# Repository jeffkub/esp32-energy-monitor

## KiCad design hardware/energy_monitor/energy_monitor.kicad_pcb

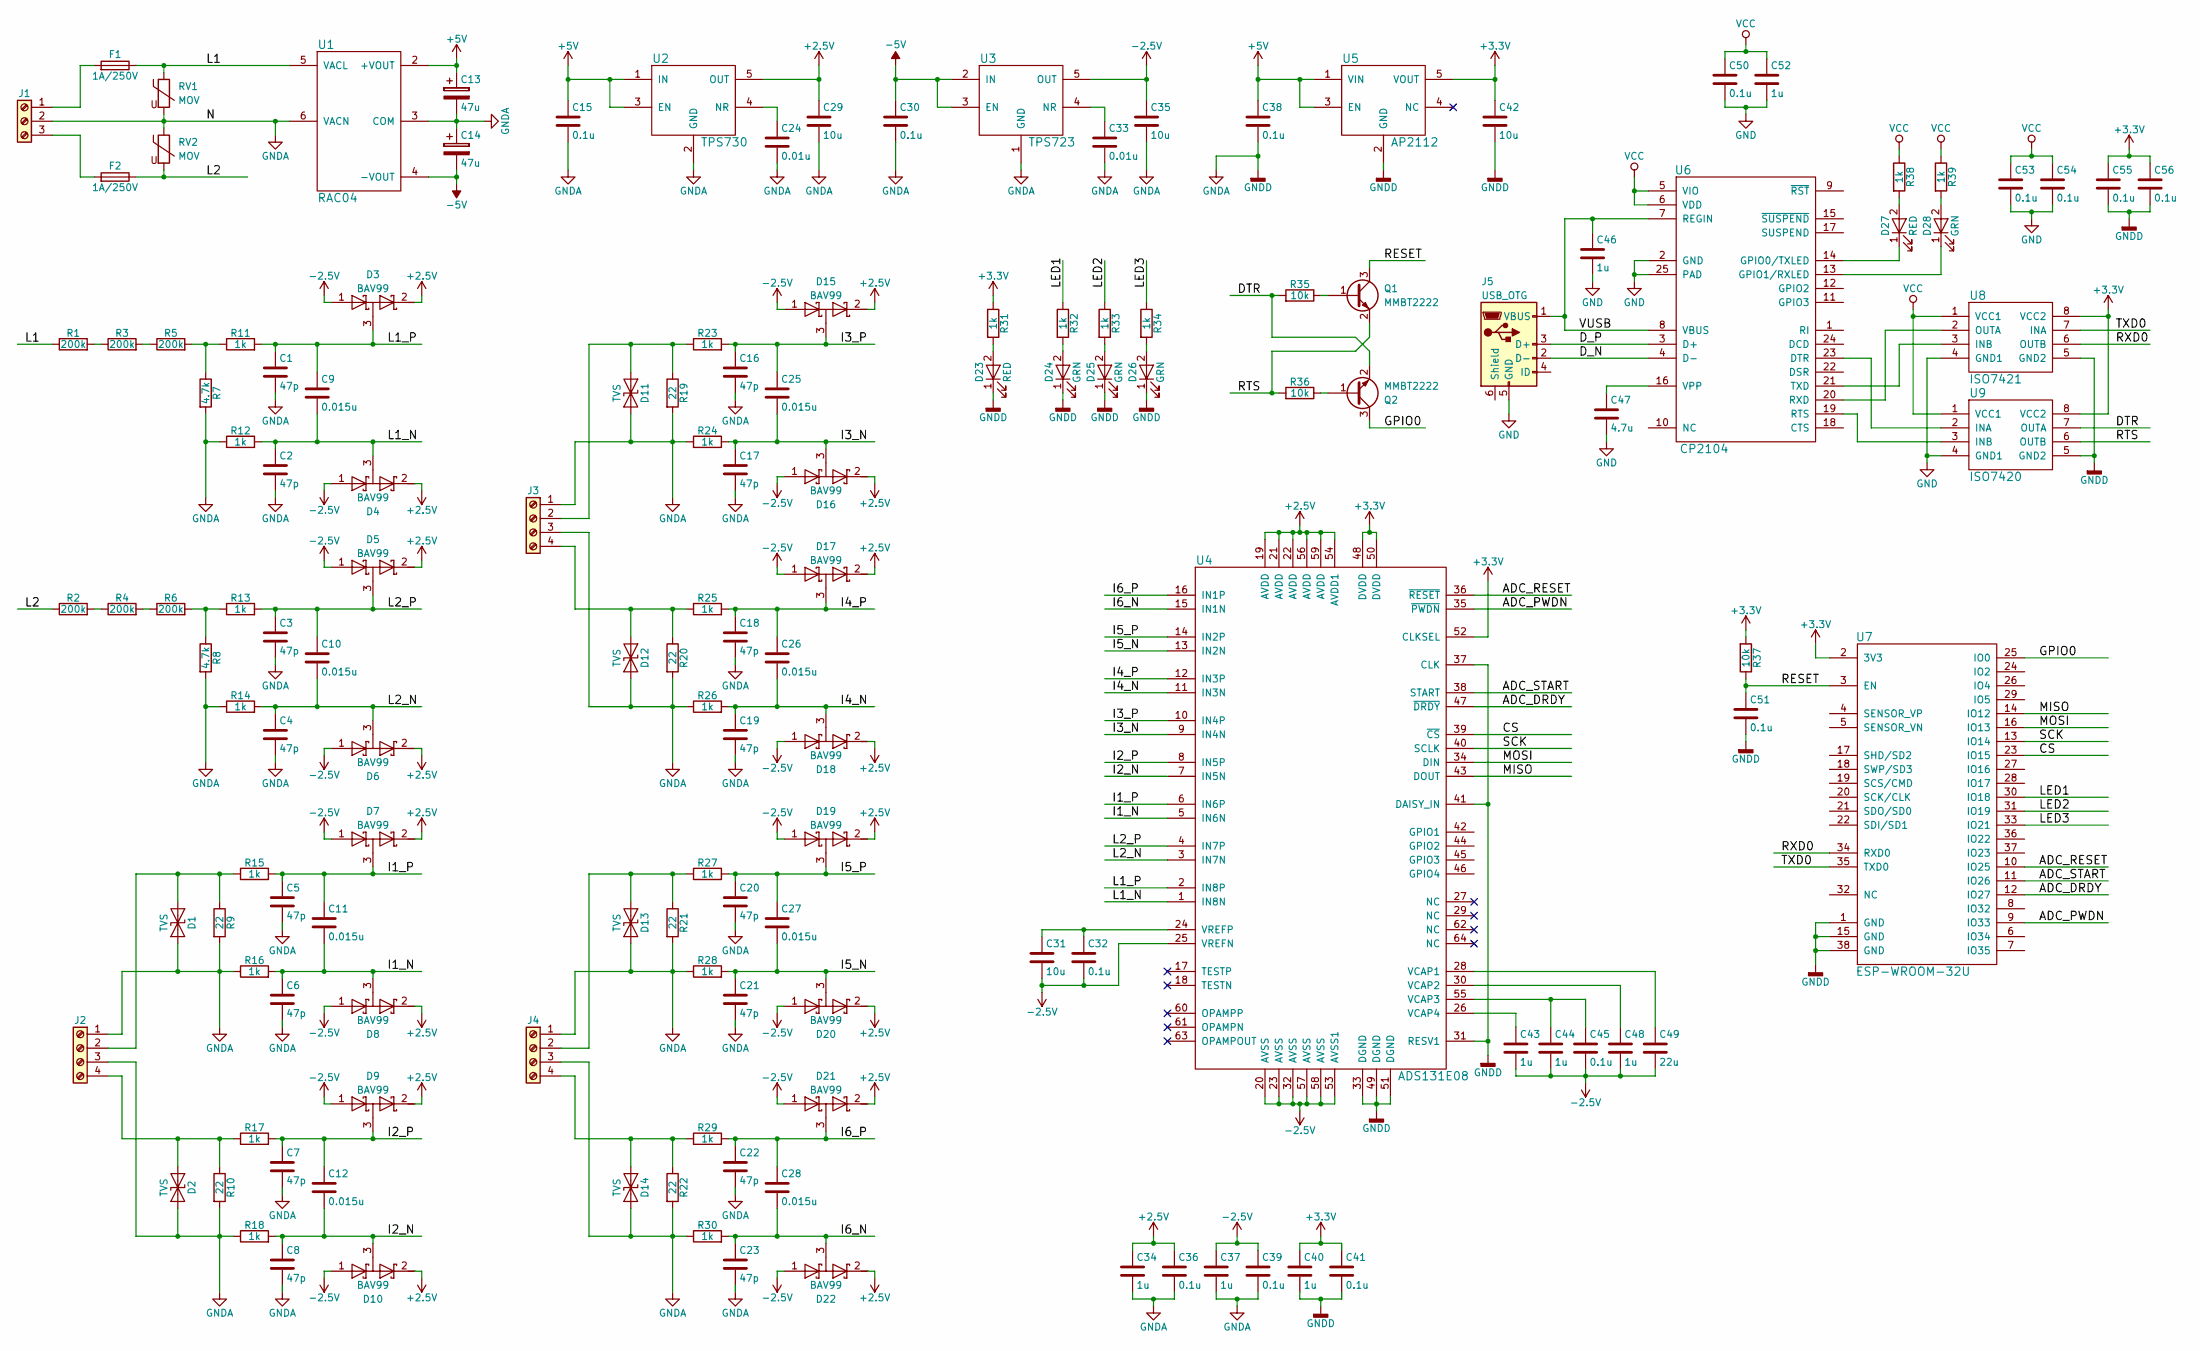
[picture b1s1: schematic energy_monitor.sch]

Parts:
C1, C2, C3, C4, C5, C6, C7, C8, C16, C17, C18, C19, C20, C21, C22, C23: 47p; C_0603; Part 490-4944-1-ND
C9, C10, C11, C12, C25, C26, C27, C28: 0.015u; C_0603; Part 490-6054-1-ND
C13, C14: 47u; CP_Elec_6.3x5.8; Part PCE3889CT-ND
C15, C30, C32, C36, C38, C39, C41, C45, C50, C51, C53, C54, C55, C56: 0.1u; C_0603; Part 490-9691-1-ND
C24, C33: 0.01u; C_0603; Part 490-1520-1-ND
C29, C31, C35, C42: 10u; C_0805; Part 490-5523-1-ND
C34, C37, C40, C43, C44, C46, C48, C52: 1u; C_0805; Part 490-1691-1-ND
C47: 4.7u; C_0805; Part 490-5422-1-ND
C49: 22u; C_1206; Part 490-8342-1-ND
D1, D2, D11, D12, D13, D14: TVS; D_SMA; Part SMAJ5.0CA-FDICT-ND
D3, D4, D5, D6, D7, D8, D9, D10, D15, D16, D17, D18, D19, D20, D21, D22: BAV99; SOT-23; Part BAV99-FDICT-ND
D23, D27: RED; D_0603; Part 160-1447-1-ND
D24, D25, D26, D28: GRN; D_0603; Part 160-1435-1-ND
F1, F2: 1A/250V; Fuse_Littelfuse-443; Part F2906CT-ND
J1: Screw_Terminal_01x03; TerminalBlock_03x5.08mm; Part 277-1264-ND
J2, J3, J4: Screw_Terminal_01x04; TerminalBlock_04x5.08mm; Part 277-1265-ND
J5: USB_OTG; UX60-MB-5ST; Part H2959CT-ND
Q1, Q2: MMBT2222; SOT-23; Part MMBT2222ALT3GOSCT-ND
R1, R2, R3, R4, R5, R6: 200k; R_1206; Part 311-200KFRCT-ND
R7, R8: 4.7k; R_1206; Part YAG2054CT-ND
R9, R10, R19, R20, R21, R22: 22; R_1206; Part YAG3847CT-ND
R11, R12, R13, R14, R15, R16, R17, R18, R23, R24, R25, R26, R27, R28, R29, R30, R31, R32, R33, R34, R38, R39: 1k; R_0603; Part 311-1.00KHRCT-ND
R35, R36, R37: 10k; R_0603; Part 311-10.0KHRCT-ND
RV1, RV2: MOV; RV_Disc_D12_W5_P7.5; Part P7207-ND
U1: RAC04; Part 945-2415-5-ND
U2: TPS730; SOT-23-5; Part 296-17578-1-ND
U3: TPS723; SOT-23-5; Part 296-39479-1-ND
U4: ADS131E08; TQFP-64_10x10mm_Pitch0.5mm; Part 296-43796-5-ND
U5: AP2112; SOT-23-5; Part AP2112K-3.3TRG1DICT-ND
U6: CP2104; QFN-24-1EP_4x4mm_Pitch0.5mm; Part 336-2008-5-ND
U7: ESP-WROOM-32U; ESP32-WROOM-32U
U8: ISO7421; SOIC-8_3.9x4.9mm_Pitch1.27mm; Part 296-38564-1-ND
U9: ISO7420; SOIC-8_3.9x4.9mm_Pitch1.27mm; Part 296-28742-1-ND

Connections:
+2.5V: C29.1, C34.1, C36.1, D3.2 (K), D4.2 (K), D5.2 (K), D6.2 (K), D7.2 (K), D8.2 (K), D9.2 (K), D10.2 (K), D15.2 (K), D16.2 (K), D17.2 (K), D18.2 (K), D19.2 (K), D20.2 (K), D21.2 (K), D22.2 (K), U2.5 (OUT), U4.19 (AVDD), U4.21 (AVDD), U4.22 (AVDD), U4.54 (AVDD1), U4.56 (AVDD), U4.59 (AVDD)
+3V3: C40.1, C41.1, C42.1, C55.1, C56.1, R31.1, R37.2, U4.48 (DVDD), U4.50 (DVDD), U4.52 (CLKSEL), U5.5 (VOUT), U7.2 (3V3), U8.8 (VCC2), U9.8 (VCC2)
+5V: C13.1, C15.1, C38.1, U1.2 (+VOUT), U2.1 (IN), U2.3 (EN), U5.1 (VIN), U5.3 (EN)
-2.5V: C31.2, C32.2, C35.1, C37.1, C39.1, C43.2, C44.2, C45.2, C48.2, C49.2, D3.1 (A), D4.1 (A), D5.1 (A), D6.1 (A), D7.1 (A), D8.1 (A), D9.1 (A), D10.1 (A), D15.1 (A), D16.1 (A), D17.1 (A), D18.1 (A), D19.1 (A), D20.1 (A), D21.1 (A), D22.1 (A), U3.5 (OUT), U4.20 (AVSS), U4.23 (AVSS), U4.25 (VREFN), U4.32 (AVSS), U4.53 (AVSS1), U4.57 (AVSS), U4.58 (AVSS)
-5V: C14.2, C30.1, U1.4 (-VOUT), U3.2 (IN), U3.3 (EN)
/ADC_DRDY: U4.47 (~DRDY), U7.12 (IO27)
/ADC_PWDN: U4.35 (~PWDN), U7.9 (IO33)
/ADC_RESET: U4.36 (~RESET), U7.10 (IO25)
/ADC_START: U4.38 (START), U7.11 (IO26)
/CS: U4.39 (~CS), U7.23 (IO15)
/DTR: Q2.2 (E), R35.2, U9.7 (OUTA)
/D_N: J5.2 (D-), U6.4 (D-)
/D_P: J5.3 (D+), U6.3 (D+)
/GPIO0: Q2.3 (C), U7.25 (IO0)
/I1_N: C6.1, C11.2, D8.3 (common), R16.2, U4.5 (IN6N)
/I1_P: C5.1, C11.1, D7.3 (common), R15.2, U4.6 (IN6P)
/I2_N: C8.1, C12.2, D10.3 (common), R18.2, U4.7 (IN5N)
/I2_P: C7.1, C12.1, D9.3 (common), R17.2, U4.8 (IN5P)
/I3_N: C17.1, C25.2, D16.3 (common), R24.2, U4.9 (IN4N)
/I3_P: C16.1, C25.1, D15.3 (common), R23.2, U4.10 (IN4P)
/I4_N: C19.1, C26.2, D18.3 (common), R26.2, U4.11 (IN3N)
/I4_P: C18.1, C26.1, D17.3 (common), R25.2, U4.12 (IN3P)
/I5_N: C21.1, C27.2, D20.3 (common), R28.2, U4.13 (IN2N)
/I5_P: C20.1, C27.1, D19.3 (common), R27.2, U4.14 (IN2P)
/I6_N: C23.1, C28.2, D22.3 (common), R30.2, U4.15 (IN1N)
/I6_P: C22.1, C28.1, D21.3 (common), R29.2, U4.16 (IN1P)
/L1: F1.1, R1.1, RV1.1, U1.5 (VACL)
/L1_N: C2.1, C9.2, D4.3 (common), R12.2, U4.1 (IN8N)
/L1_P: C1.1, C9.1, D3.3 (common), R11.2, U4.2 (IN8P)
/L2: F2.1, R2.1, RV2.2
/L2_N: C4.1, C10.2, D6.3 (common), R14.2, U4.3 (IN7N)
/L2_P: C3.1, C10.1, D5.3 (common), R13.2, U4.4 (IN7P)
/LED1: R32.1, U7.30 (IO18)
/LED2: R33.1, U7.31 (IO19)
/LED3: R34.1, U7.33 (IO21)
/MISO: U4.43 (DOUT), U7.14 (IO12)
/MOSI: U4.34 (DIN), U7.16 (IO13)
/RESET: C51.1, Q1.3 (C), R37.1, U7.3 (EN)
/RTS: Q1.2 (E), R36.2, U9.6 (OUTB)
/RXD0: U7.34 (RXD0), U8.6 (OUTB)
/SCK: U4.40 (SCLK), U7.13 (IO14)
/TXD0: U7.35 (TXD0), U8.7 (INA)
/VUSB: C46.1, J5.1 (VBUS), U6.7 (REGIN), U6.8 (VBUS)
GND: C46.2, C47.2, C50.2, C52.2, C53.2, C54.2, J5.5 (GND), U6.2 (GND), U6.25 (PAD), U8.4 (GND1), U9.4 (GND1)
GNDA: C1.2, C2.2, C3.2, C4.2, C5.2, C6.2, C7.2, C8.2, C13.2, C14.1, C15.2, C16.2, C17.2, C18.2, C19.2, C20.2, C21.2, C22.2, C23.2, C24.2, C29.2, C30.2, C33.2, C34.2, C35.2, C36.2, C37.2, C38.2, C39.2, C40.2, C41.2, C42.2, C51.2, C55.2, C56.2, D1.1 (A1), D2.1 (A1), D11.1 (A1), D12.1 (A1), D13.1 (A1), D14.1 (A1), D23.1 (K), D24.1 (K), D25.1 (K), D26.1 (K), J1.2, J2.1, J2.3, J3.1, J3.3, J4.1, J4.3, R7.2, R8.2, R9.2, R10.2, R12.1, R14.1, R16.1, R18.1, R19.2, R20.2, R21.2, R22.2, R24.1, R26.1, R28.1, R30.1, RV1.2, RV2.1, U1.3 (COM), U1.6 (VACN), U2.2 (GND), U3.1 (GND), U4.31 (RESV1), U4.33 (DGND), U4.37 (CLK), U4.41 (DAISY_IN), U4.49 (DGND), U4.51 (DGND), U5.2 (GND), U7.1 (GND), U7.15 (GND), U7.38 (GND), U8.5 (GND2), U9.5 (GND2)
unnamed: C24.1, U2.4 (NR)
unnamed: C31.1, C32.1, U4.24 (VREFP)
unnamed: C33.1, U3.4 (NR)
unnamed: C43.1, U4.26 (VCAP4)
unnamed: C44.1, C45.1, U4.55 (VCAP3)
unnamed: C47.1, U6.16 (VPP)
unnamed: C48.1, U4.30 (VCAP2)
unnamed: C49.1, U4.28 (VCAP1)
unnamed: D1.2 (A2), J2.2, R9.1, R15.1
unnamed: D2.2 (A2), J2.4, R10.1, R17.1
unnamed: D11.2 (A2), J3.2, R19.1, R23.1
unnamed: D12.2 (A2), J3.4, R20.1, R25.1
unnamed: D13.2 (A2), J4.2, R21.1, R27.1
unnamed: D14.2 (A2), J4.4, R22.1, R29.1
unnamed: D23.2 (A), R31.2
unnamed: D24.2 (A), R32.2
unnamed: D25.2 (A), R33.2
unnamed: D26.2 (A), R34.2
unnamed: D27.1 (K), U6.14 (GPIO0/TXLED)
unnamed: D27.2 (A), R38.2
unnamed: D28.1 (K), U6.13 (GPIO1/RXLED)
unnamed: D28.2 (A), R39.2
unnamed: F1.2, J1.1
unnamed: F2.2, J1.3
unnamed: Q1.1 (B), R35.1
unnamed: Q2.1 (B), R36.1
unnamed: R1.2, R3.1
unnamed: R2.2, R4.1
unnamed: R3.2, R5.1
unnamed: R4.2, R6.1
unnamed: R5.2, R7.1, R11.1
unnamed: R6.2, R8.1, R13.1
unnamed: U6.19 (RTS), U9.3 (INB)
unnamed: U6.20 (RXD), U8.2 (OUTA)
unnamed: U6.21 (TXD), U8.3 (INB)
unnamed: U6.23 (DTR), U9.2 (INA)
VCC: C50.1, C52.1, C53.1, C54.1, R38.1, R39.1, U6.5 (VIO), U6.6 (VDD), U8.1 (VCC1), U9.1 (VCC1)

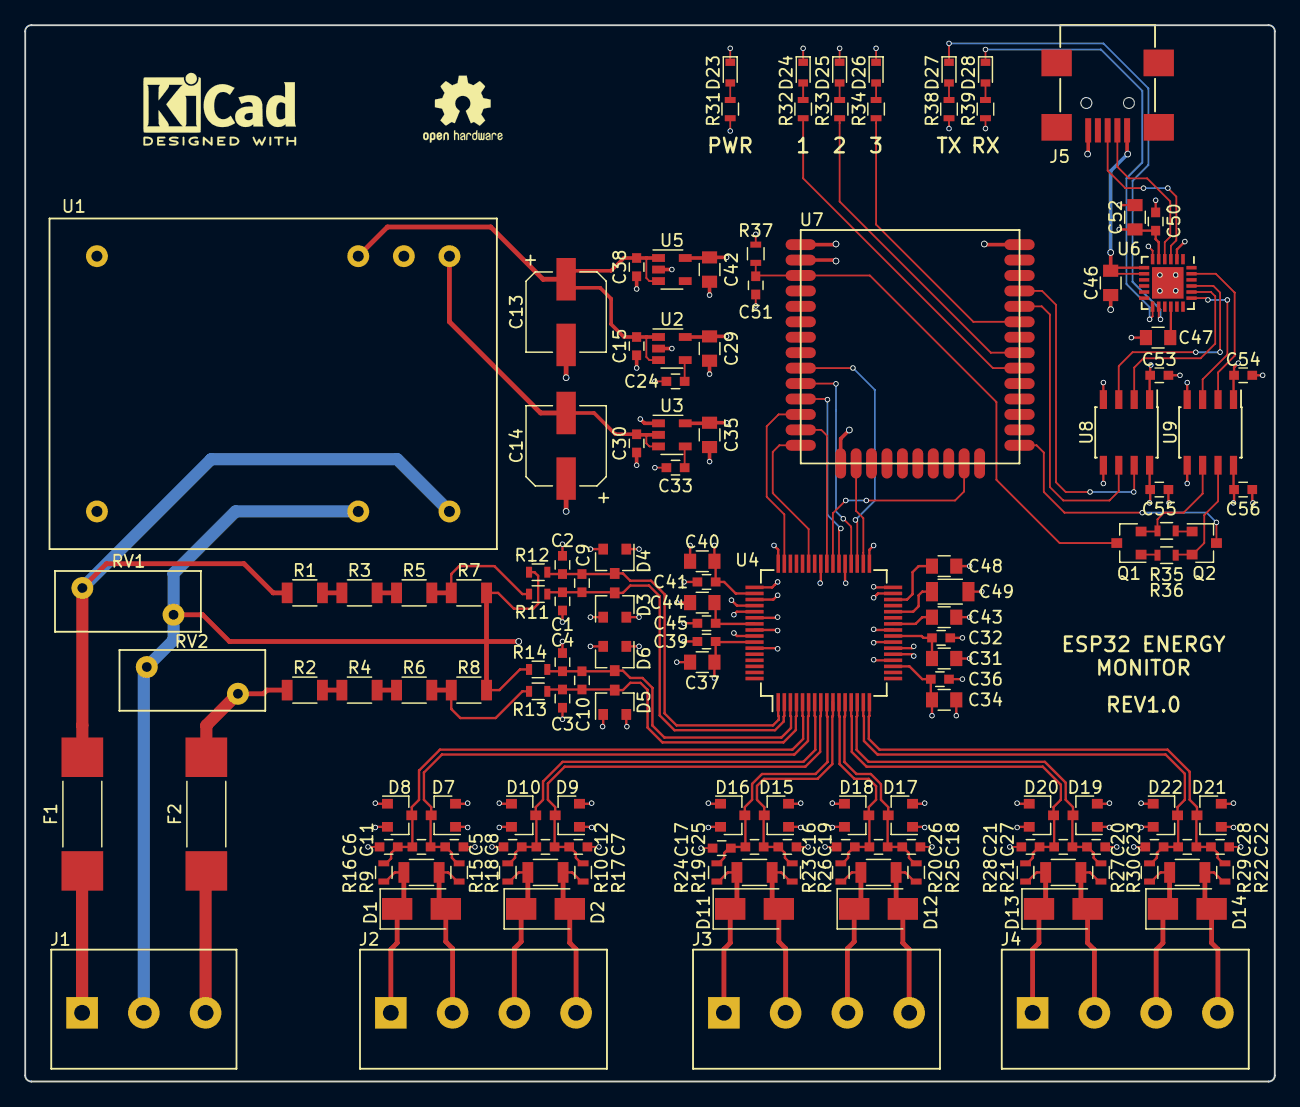
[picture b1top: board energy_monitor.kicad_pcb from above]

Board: 4 copper layers, 102.8 x 86.9 mm, 143 parts (0 on the bottom side), 82 nets.

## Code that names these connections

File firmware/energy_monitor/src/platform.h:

#ifndef _PROJECT_H_
#define _PROJECT_H_

#include <driver/gpio.h>

#define LED1_PIN        GPIO_NUM_18
#define LED2_PIN        GPIO_NUM_19
#define LED3_PIN        GPIO_NUM_21

#define CS_PIN          GPIO_NUM_15
#define SCK_PIN         GPIO_NUM_14
#define MOSI_PIN        GPIO_NUM_13
#define MISO_PIN        GPIO_NUM_12

#define ADC_RESET_PIN   GPIO_NUM_25
#define ADC_PWDN_PIN    GPIO_NUM_33
#define ADC_START_PIN   GPIO_NUM_26
#define ADC_DRDY_PIN    GPIO_NUM_27

#define DEBUG1_PIN      GPIO_NUM_22
#define DEBUG2_PIN      GPIO_NUM_23

/* Debug macros */
#define SET_DEBUG1()    GPIO.out_w1ts = (1 << DEBUG1_PIN)
#define CLR_DEBUG1()    GPIO.out_w1tc = (1 << DEBUG1_PIN)

#define SET_DEBUG2()    GPIO.out_w1ts = (1 << DEBUG2_PIN)
#define CLR_DEBUG2()    GPIO.out_w1tc = (1 << DEBUG2_PIN)

#endif /* #ifndef _PROJECT_H_ */

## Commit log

2018-06-02 Added kicad-libs submodule
2018-06-02 Created KiCad project
2018-06-02 Created ADS131E08 symbol
2018-06-03 Working on schematic
2018-06-03 Added footprints and part numbers for signal conditioning circuits
2018-06-05 Working on BOM and assigning footprints
2018-06-05 Updated PDF
2018-06-06 Working on footprints
2018-06-07 Exported netlist. Working on layout
2018-06-07 Working on layout
2018-06-08 Configured design rules
2018-06-09 Working on layout. Removed 0.1u caps on 5V output
2018-06-09 Switched 3.5mm jacks to terminal blocks
2018-06-09 Added digital isolator to USB UART circuit
2018-06-11 Finished routing board
2018-06-11 Fixed silkscreen layers
2018-06-12 Added 2 more LEDs. Added labels to LEDs. Added board rev #
2018-06-12 Rounded the corners
2018-06-13 Minor PCB tweaks and created gerbers
2018-06-15 Created project with blinky task
2018-06-17 Created class for adc driver
2018-06-17 working on adc driver
2018-06-19 Minor fix
2018-07-13 Changed to SPI mode 1, able to read ID register
2018-07-14 Added method to set VRef source
2018-07-14 Added task to test ADC driver
2018-07-21 ADC read is now working
2018-07-22 Fixed IRQ/semaphore issues with ADC driver
2018-07-22 Created Data Acquisition class
2018-07-23 Moved ADC test code into DAQ class
2018-07-23 Implemented RMS data processor class
2018-07-24 Created SPI driver class
2018-07-24 Working on spi driver
2018-07-24 Cleaning up SPI driver code
2018-07-25 Implemented setClock method
2018-07-25 Added function to set SPI mode
2018-07-29 Optimizing SPI driver
2018-08-01 Modified AD131 driver to use ESP32 SPI driver
2018-08-02 ADS131 driver now working with new SPI driver
2018-08-02 Added debug pin GPIO config
2018-08-12 Added task to print DAQ values periodically
2018-08-13 Working on data processores
2018-08-13 Added scaling factor for voltage/ current inputs
